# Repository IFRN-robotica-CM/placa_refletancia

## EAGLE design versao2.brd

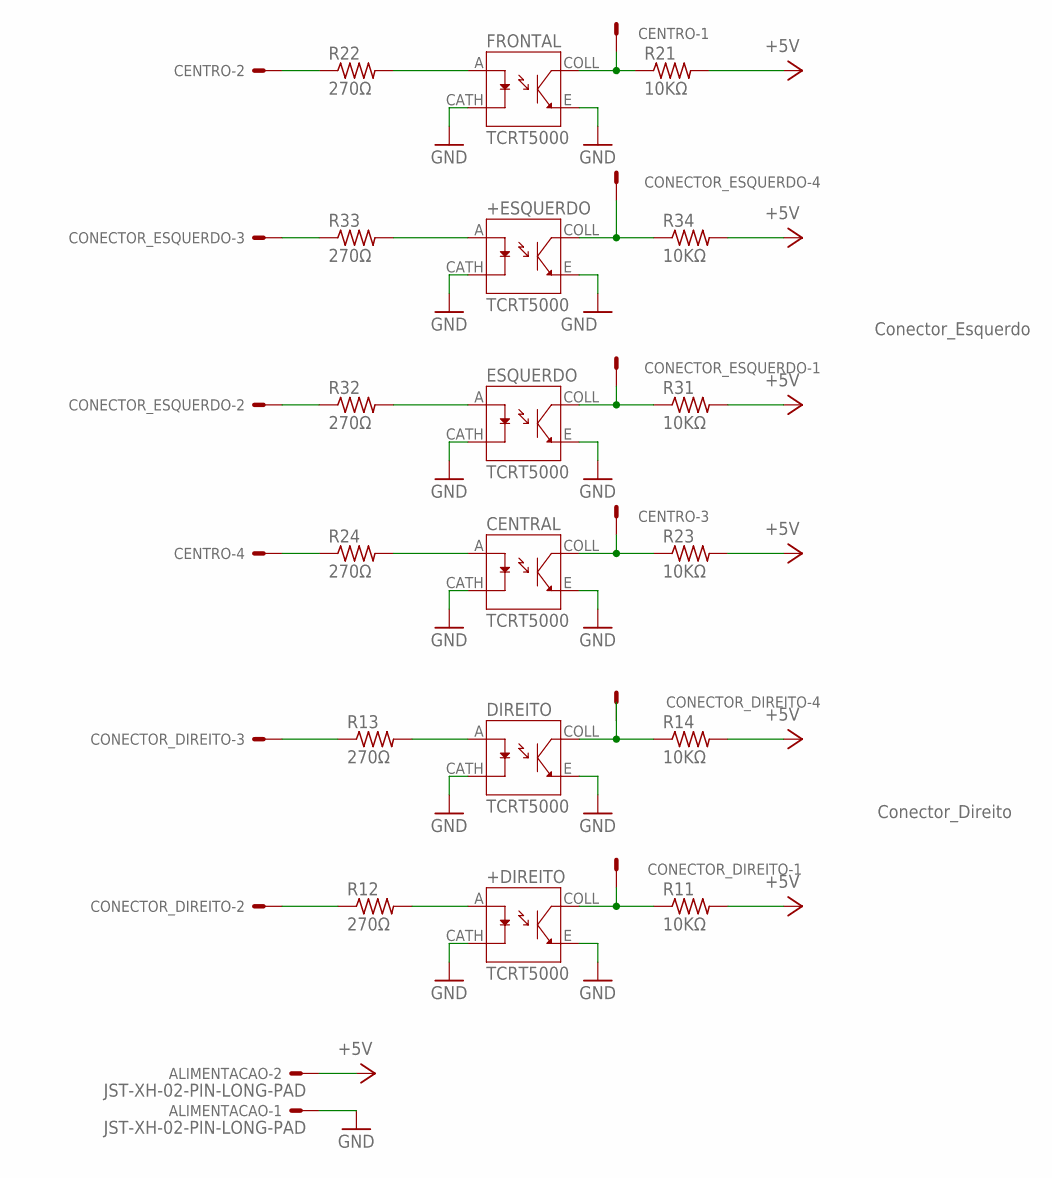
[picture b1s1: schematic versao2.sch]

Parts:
+DIREITO: TCRT5000; OPTO_TCRT5000
+ESQUERDO: TCRT5000; OPTO_TCRT5000
ALIMENTACAO: JST-XH-02-PIN-LONG-PAD; JST-XH-02-PACKAGE-LONG-PAD
CENTRAL: TCRT5000; OPTO_TCRT5000
CENTRO: JST-XH-04-PIN-LONG-PAD; JST-XH-04-PACKAGE-LONG-PAD
CONECTOR_DIREITO: Conector_Direito; JST-XH-04-PACKAGE-LONG-PAD
CONECTOR_ESQUERDO: Conector_Esquerdo; JST-XH-04-PACKAGE-LONG-PAD
DIREITO: TCRT5000; OPTO_TCRT5000
ESQUERDO: TCRT5000; OPTO_TCRT5000
FRONTAL: TCRT5000; OPTO_TCRT5000
R11, R14, R21, R23, R31, R34: 10KΩ; 0204/7
R12, R13, R22, R24, R32, R33: 270Ω; 0204/7

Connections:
+5V: ALIMENTACAO.2, R11.2, R14.2, R21.2, R23.2, R31.2, R34.2
ANALOG+ESQ: +ESQUERDO.COLL, CONECTOR_ESQUERDO.4, R34.1
ANALOG_+DI: +DIREITO.COLL, CONECTOR_DIREITO.1, R11.1
ANALOG_CE: CENTRAL.COLL, CENTRO.3, R23.1
ANALOG_DI: CONECTOR_DIREITO.4, DIREITO.COLL, R14.1
ANALOG_ESQ: CONECTOR_ESQUERDO.1, ESQUERDO.COLL, R31.1
ANALOG_FR: CENTRO.1, FRONTAL.COLL, R21.1
CENTRAL: CENTRAL.A, R24.2
DIGITA+ESQ: +ESQUERDO.A, R33.2
DIGITAL: ESQUERDO.A, R32.2
DIGITAL+DIR: +DIREITO.A, R12.2
DIGITAL+ESQ: CONECTOR_ESQUERDO.3, R33.1
DIGITAL_+DI: CONECTOR_DIREITO.2, R12.1
DIGITAL_CE: CENTRO.4, R24.1
DIGITAL_DI: CONECTOR_DIREITO.3, R13.1
DIGITAL_ESQ: CONECTOR_ESQUERDO.2, R32.1
DIGITAL_FR: FRONTAL.A, R22.2
DIGTAL-DI: DIREITO.A, R13.2
FRONTAL: CENTRO.2, R22.1
GND: +DIREITO.CATH, +DIREITO.E, +ESQUERDO.CATH, +ESQUERDO.E, ALIMENTACAO.1, CENTRAL.CATH, CENTRAL.E, DIREITO.CATH, DIREITO.E, ESQUERDO.CATH, ESQUERDO.E, FRONTAL.CATH, FRONTAL.E

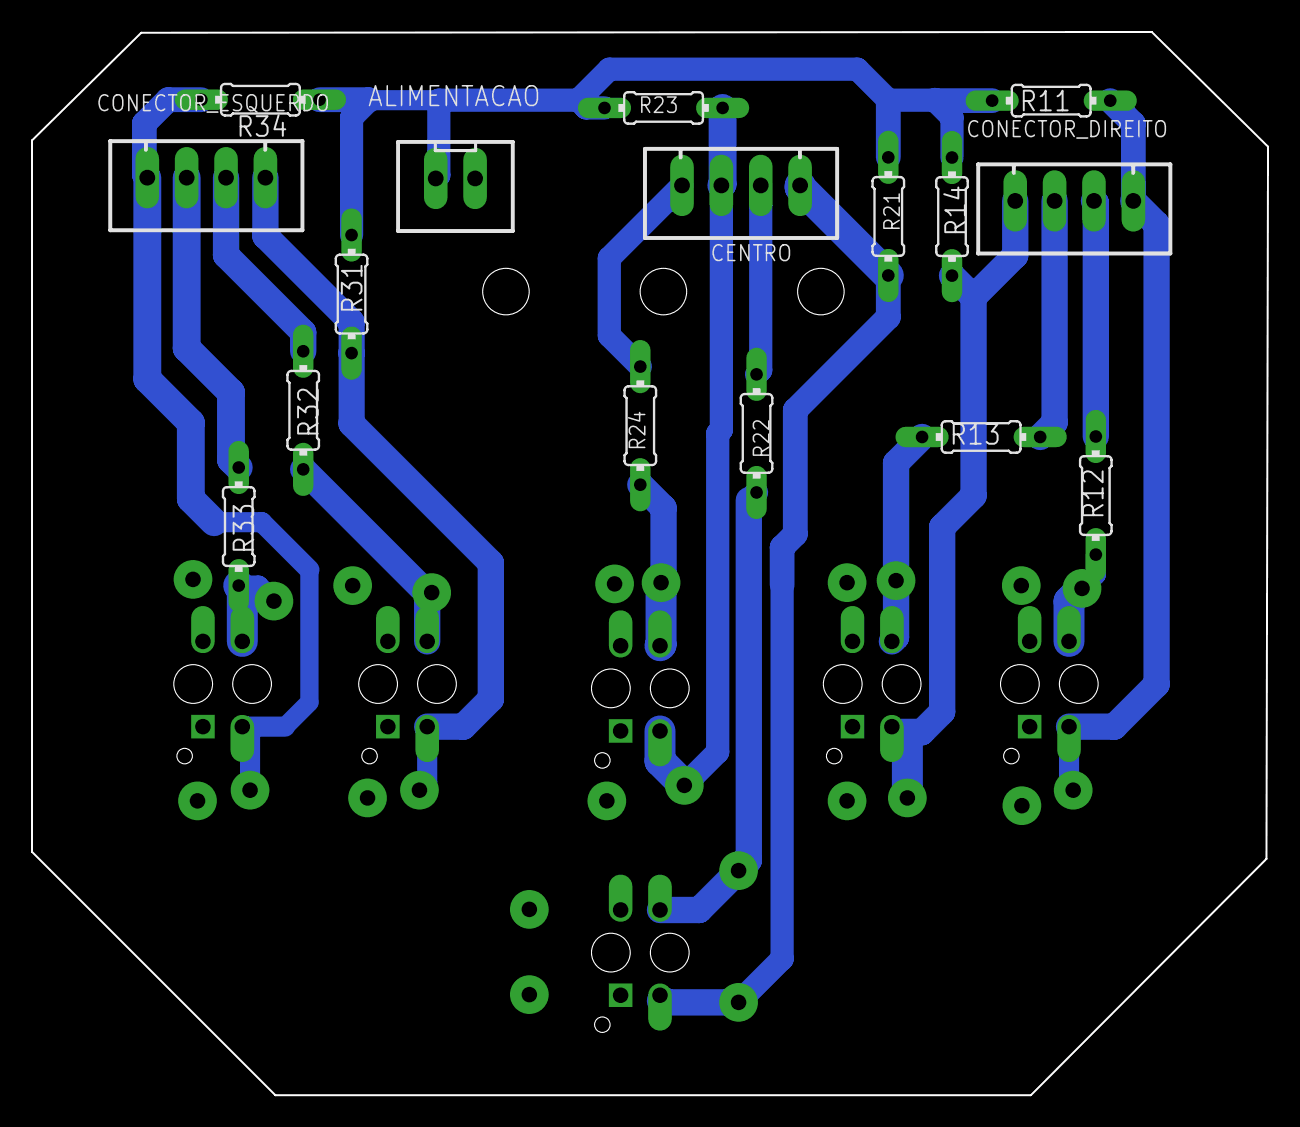
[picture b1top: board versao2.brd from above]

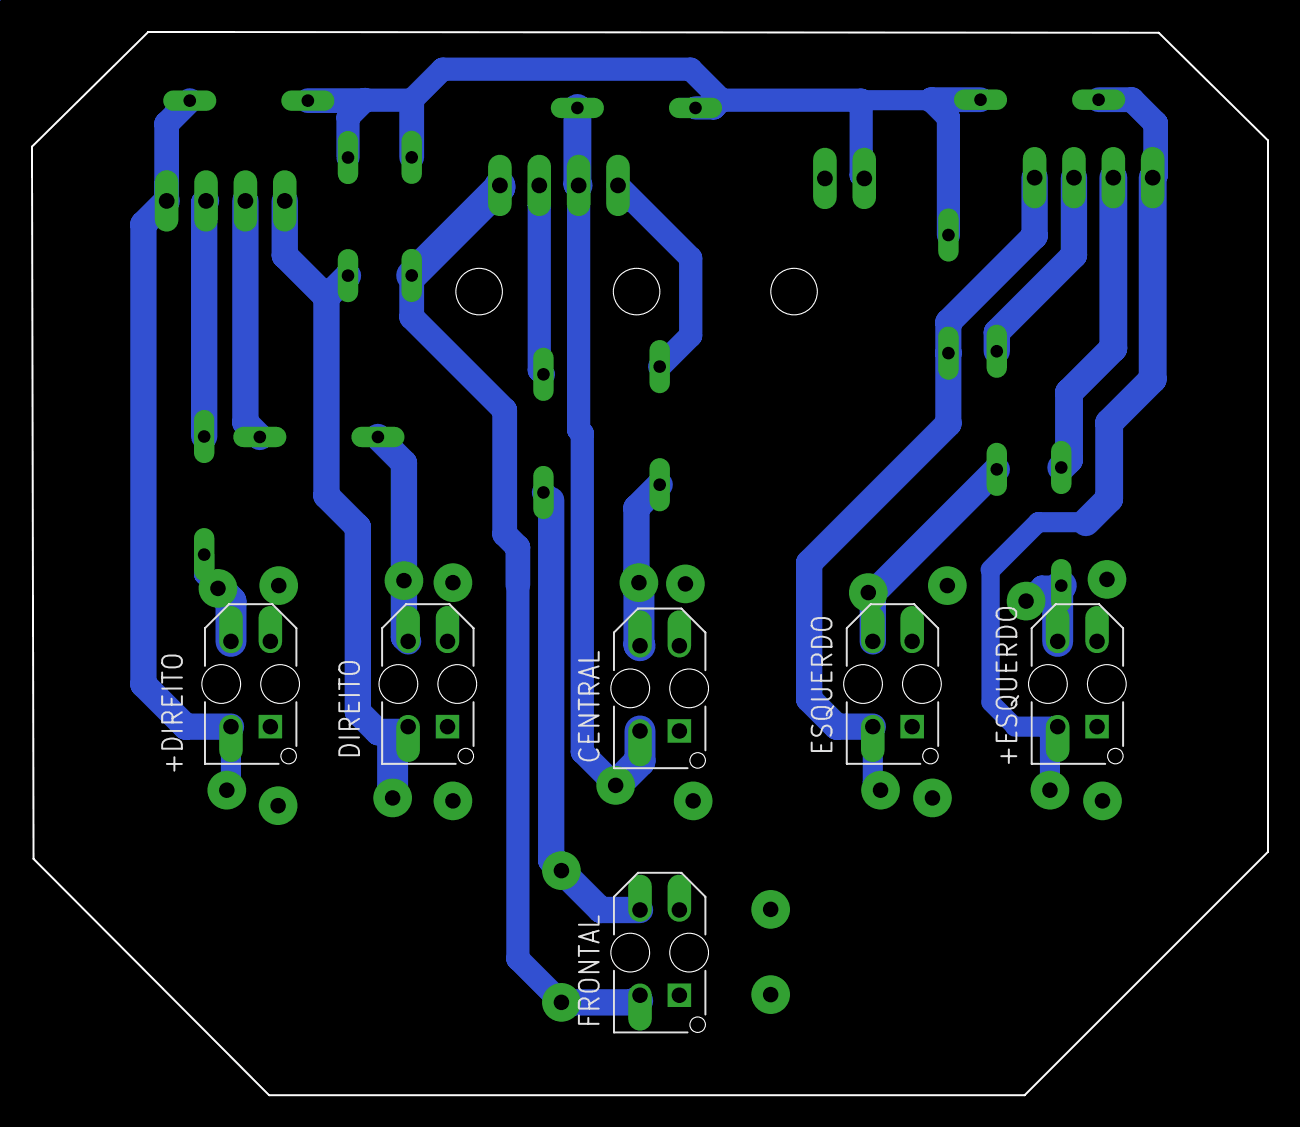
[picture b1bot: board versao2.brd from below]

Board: 2 copper layers, 79.8 x 68.6 mm, 22 parts (6 on the bottom side), 20 nets.

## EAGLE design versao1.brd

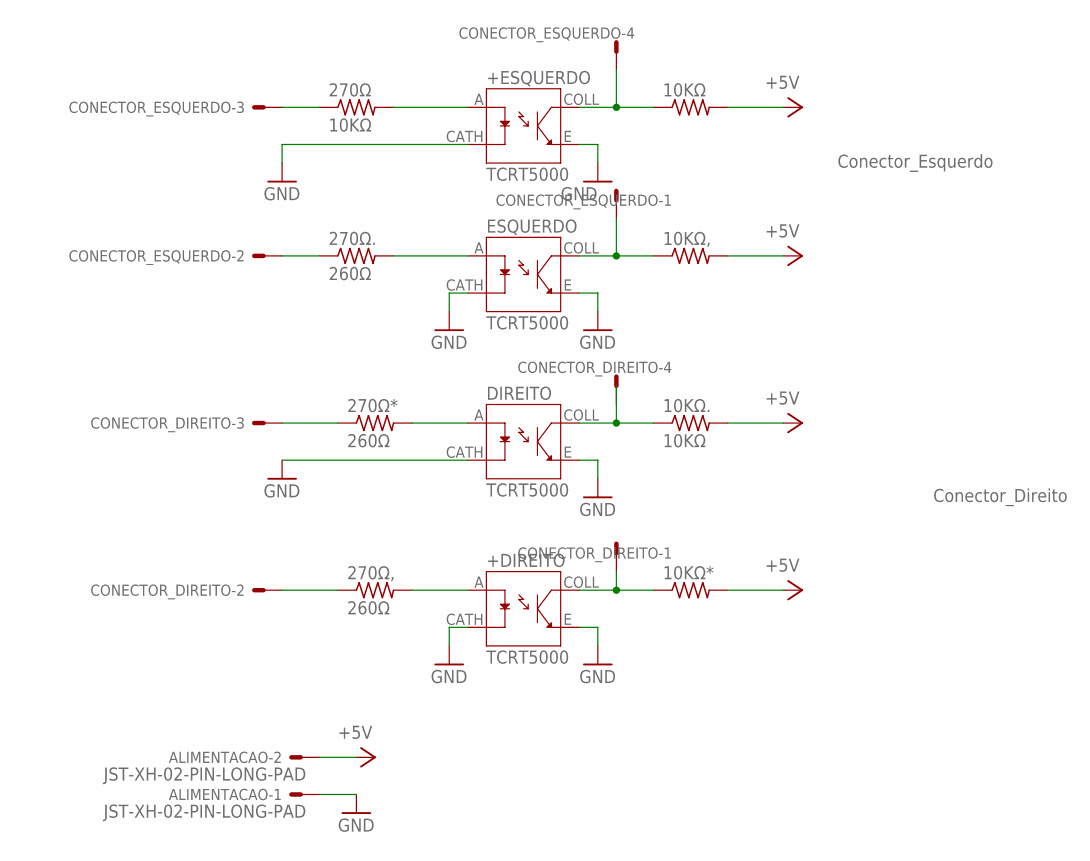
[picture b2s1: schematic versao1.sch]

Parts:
10KΩ, 10KΩ*, 10KΩ,: R-US_0204/7; 0204/7
10KΩ., 270Ω: 10KΩ; 0204/7
270Ω*, 270Ω,, 270Ω.: 260Ω; 0204/7
+DIREITO: TCRT5000; OPTO_TCRT5000
+ESQUERDO: TCRT5000; OPTO_TCRT5000
ALIMENTACAO: JST-XH-02-PIN-LONG-PAD; JST-XH-02-PACKAGE-LONG-PAD
CONECTOR_DIREITO: Conector_Direito; JST-XH-04-PACKAGE-LONG-PAD
CONECTOR_ESQUERDO: Conector_Esquerdo; JST-XH-04-PACKAGE-LONG-PAD
DIREITO: TCRT5000; OPTO_TCRT5000
ESQUERDO: TCRT5000; OPTO_TCRT5000

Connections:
+5V: 10KΩ.2, 10KΩ*.2, 10KΩ,.2, 10KΩ..2, ALIMENTACAO.2
ANALOG_+DI: 10KΩ*.1, +DIREITO.COLL, CONECTOR_DIREITO.1
ANALOG_+ESQ.: 10KΩ.1, +ESQUERDO.COLL, CONECTOR_ESQUERDO.4
ANALOG_DI: 10KΩ..1, CONECTOR_DIREITO.4, DIREITO.COLL
ANALOG_ESQ: 10KΩ,.1, CONECTOR_ESQUERDO.1, ESQUERDO.COLL
DIGITAL+ESQ.: 270Ω.1, CONECTOR_ESQUERDO.3
DIGITAL_+DI: 270Ω,.1, CONECTOR_DIREITO.2
DIGITAL_DI: 270Ω*.1, CONECTOR_DIREITO.3
DIGITAL_ESQ.: 270Ω..1, CONECTOR_ESQUERDO.2
GND: +DIREITO.CATH, +DIREITO.E, +ESQUERDO.CATH, +ESQUERDO.E, ALIMENTACAO.1, DIREITO.CATH, DIREITO.E, ESQUERDO.CATH, ESQUERDO.E
unnamed: 270Ω.2, +ESQUERDO.A
unnamed: 270Ω..2, ESQUERDO.A
unnamed: 270Ω*.2, DIREITO.A
unnamed: 270Ω,.2, +DIREITO.A

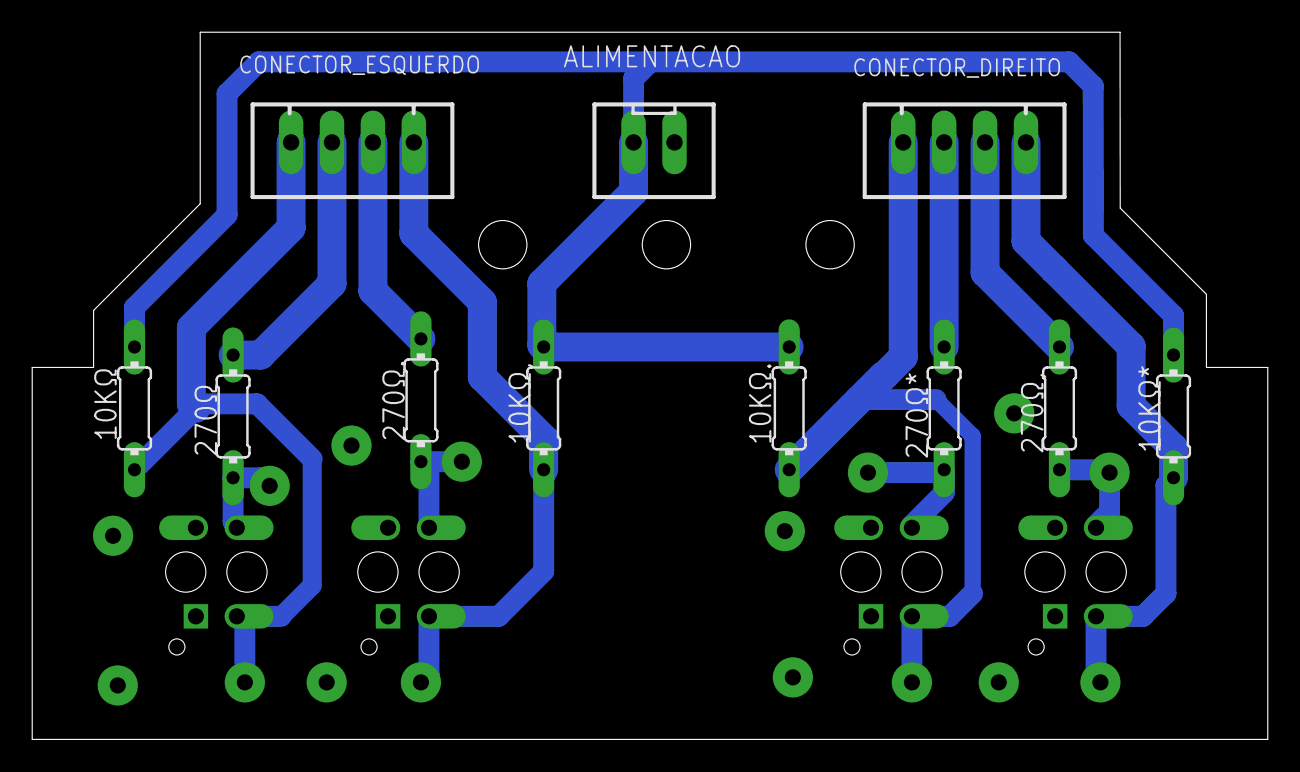
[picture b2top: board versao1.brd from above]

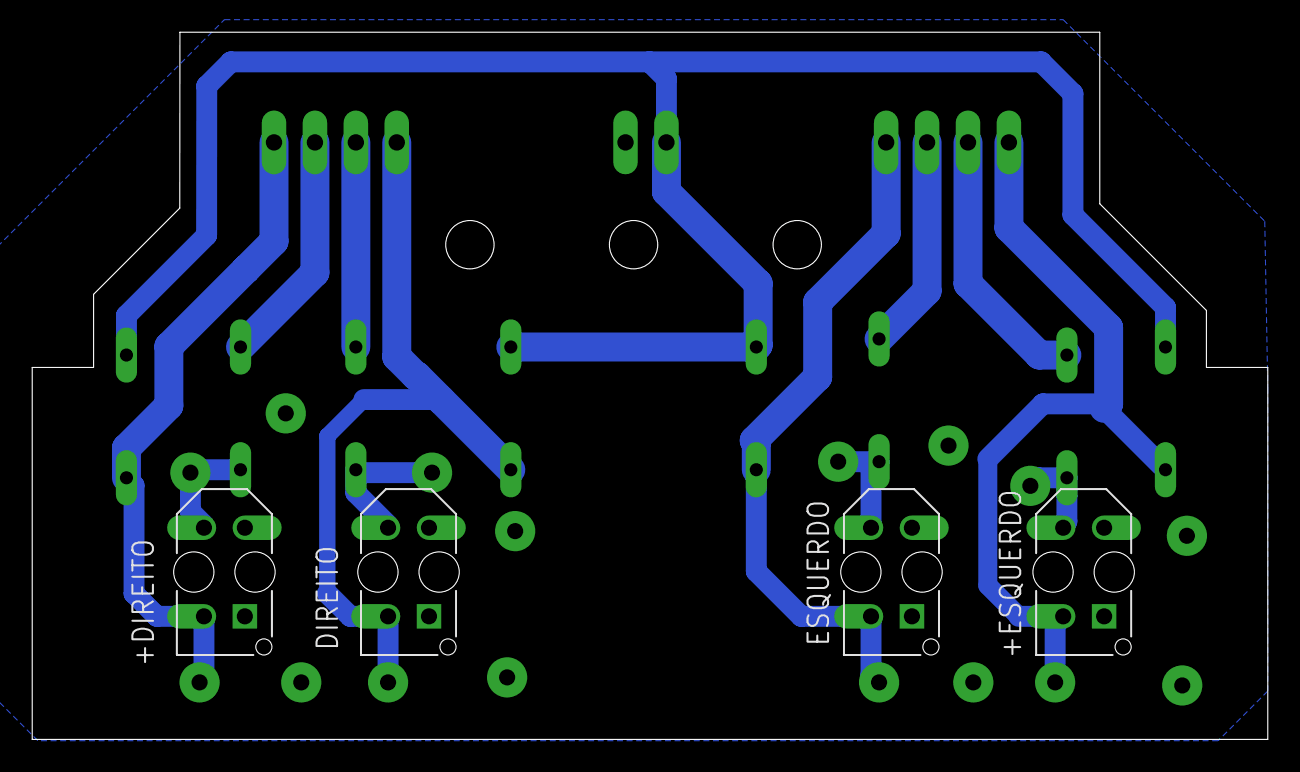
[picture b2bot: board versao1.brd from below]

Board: 2 copper layers, 76.7 x 43.9 mm, 15 parts (4 on the bottom side), 14 nets.

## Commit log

2023-12-01 adição dos primeiros arquivos iniciais
2023-12-04 organizacao da placa com 6 sensores
2024-02-22 adicionando os arquivos da placa de refletancia com 6 sensores.
